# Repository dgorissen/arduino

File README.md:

# arduino
Misc arduino projects

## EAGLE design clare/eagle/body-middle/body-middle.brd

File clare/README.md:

# C.L.A.R.E - Come Look At Robot Entertainment

CLARE, short for Come Look At Robot Entertainment, is an interactive robot I designed together with the kids and have been working on (and still am) for quite some time. Its mostly for fun and to expose the kids to robotics but also allows me to scratch that technical itch as my professional life ventures into documents, spreadsheets, powerpoint, and meetings.

I am designing CLARE fully from scratch, including all CAD, wiring, coding, custom PCBs, etc. Printing happens on my home 3D printer and features multiple cameras, face recognition and tracking, interactive voice commands, LCD screen, LEDs, and fart detector. It can be controlled with an RC remote or (planned) move autonomously using SLAM.

This is still a work in progress and updates will come whenever I find a pocket of time.

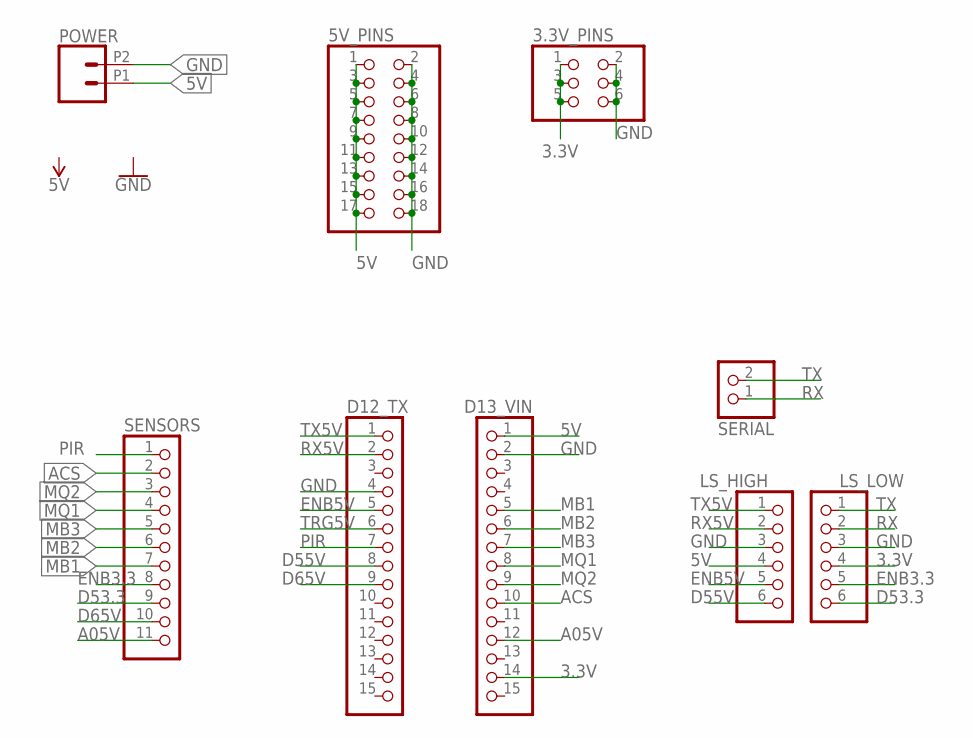
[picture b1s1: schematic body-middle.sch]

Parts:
3.3V_PINS: PINHD-2X3; 2X03
5V_PINS: PINHD-2X9; 2X09
D12_TX, D13_VIN: PINHD-1X15; 1X15
LS_HIGH: PINHD-1X6; 1X06
LS_LOW: PINHD-1X6; 1X06
POWER: CONN_022.54MM_SCREWTERM; 1X02_2.54_SCREWTERM
SENSORS: PINHD-1X11; 1X11
SERIAL: PINHD-1X2; 1X02

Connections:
3.3V: 3.3V_PINS.1, 3.3V_PINS.3, 3.3V_PINS.5, D13_VIN.14, LS_LOW.4
5V: 5V_PINS.1, 5V_PINS.3, 5V_PINS.5, 5V_PINS.7, 5V_PINS.9, 5V_PINS.11, 5V_PINS.13, 5V_PINS.15, 5V_PINS.17, D13_VIN.1, LS_HIGH.4, POWER.P1 (1)
A05V: D13_VIN.12, SENSORS.11
ACS: D13_VIN.10, SENSORS.2
D53.3: LS_LOW.6, SENSORS.9
D55V: D12_TX.8, LS_HIGH.6
D65V: D12_TX.9, SENSORS.10
ENB3.3: LS_LOW.5, SENSORS.8
ENB5V: D12_TX.5, LS_HIGH.5
GND: 3.3V_PINS.2, 3.3V_PINS.4, 3.3V_PINS.6, 5V_PINS.2, 5V_PINS.4, 5V_PINS.6, 5V_PINS.8, 5V_PINS.10, 5V_PINS.12, 5V_PINS.14, 5V_PINS.16, 5V_PINS.18, D12_TX.4, D13_VIN.2, LS_HIGH.3, LS_LOW.3, POWER.P2 (2)
MB1: D13_VIN.5, SENSORS.7
MB2: D13_VIN.6, SENSORS.6
MB3: D13_VIN.7, SENSORS.5
MQ1: D13_VIN.8, SENSORS.4
MQ2: D13_VIN.9, SENSORS.3
PIR: D12_TX.7, SENSORS.1
RX: LS_LOW.2, SERIAL.1
RX5V: D12_TX.2, LS_HIGH.2
TRG5V: D12_TX.6
TX: LS_LOW.1, SERIAL.2
TX5V: D12_TX.1, LS_HIGH.1

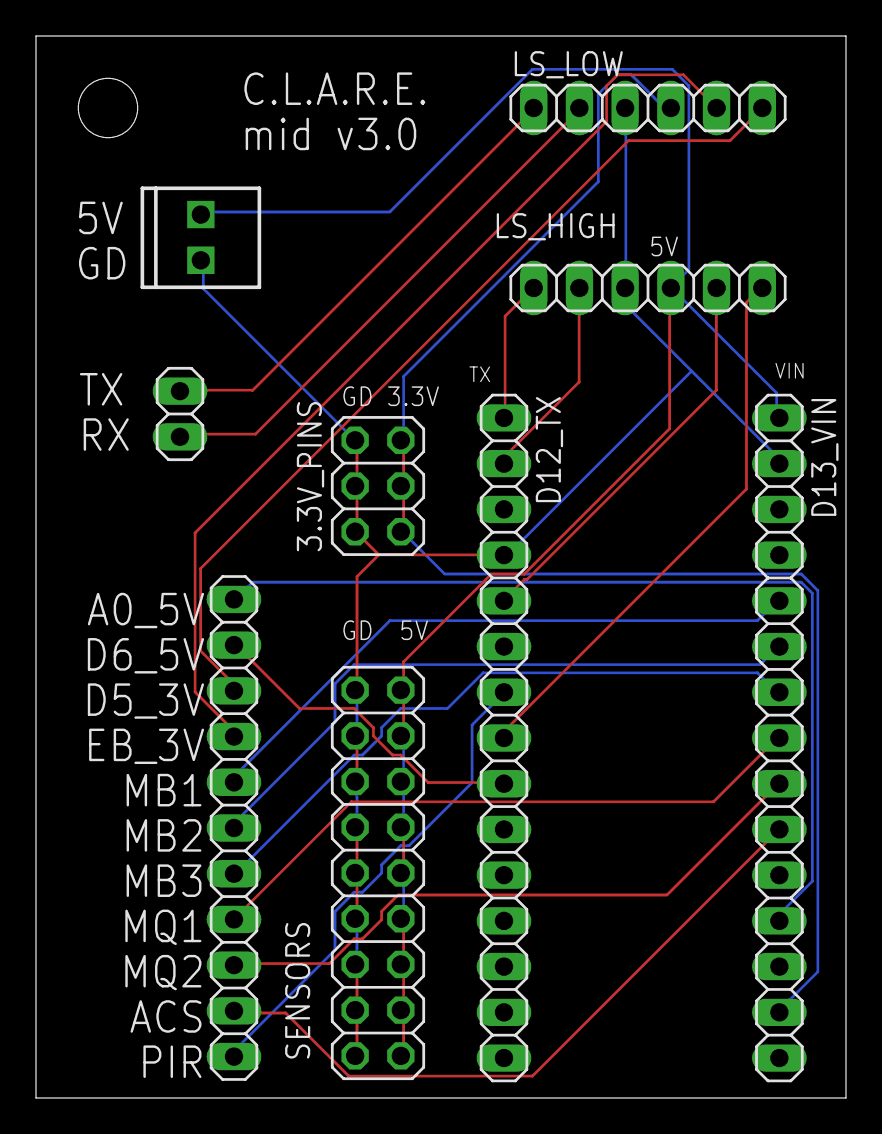
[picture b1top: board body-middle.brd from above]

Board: 2 copper layers, 45.0 x 59.0 mm, 9 parts (0 on the bottom side), 20 nets.

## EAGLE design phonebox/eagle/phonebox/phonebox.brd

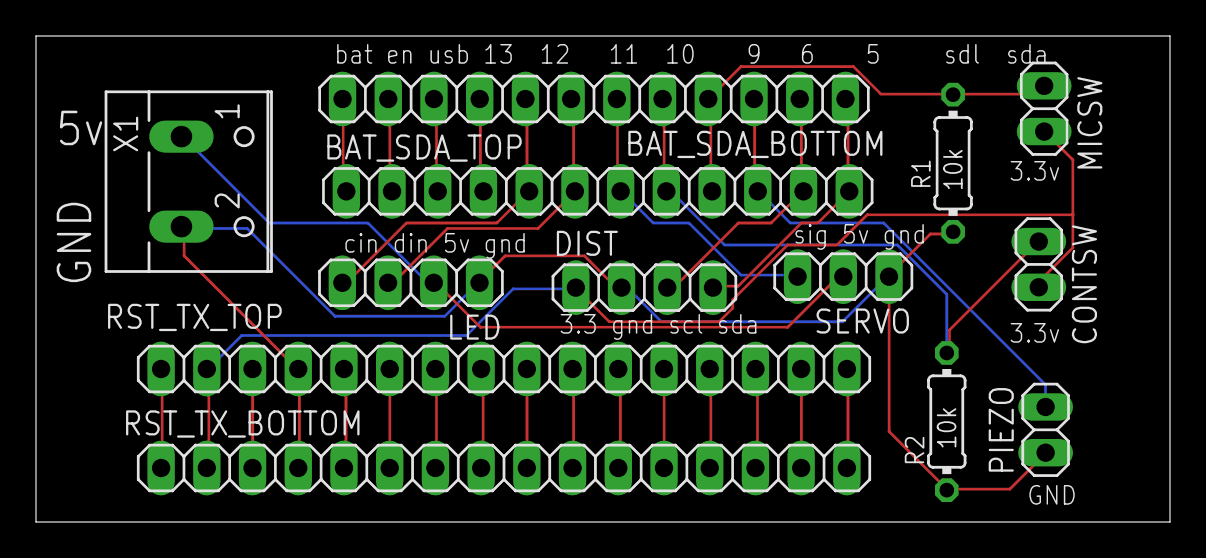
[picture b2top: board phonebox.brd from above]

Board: 2 copper layers, 63.0 x 27.0 mm, 13 parts (0 on the bottom side), 29 nets.

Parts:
BAT_SDA_BOTTOM: 1X12
BAT_SDA_TOP: 1X12
CONTSW: 1X02
DIST: 1X04
LED: 1X04
MICSW: 1X02
PIEZO: 1X02
R1, R2: 10k; 0204/7
RST_TX_BOTTOM: 1X16
RST_TX_TOP: 1X16
SERVO: 1X03
X1: W237-102

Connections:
3.3V: CONTSW.1, DIST.1, MICSW.1, RST_TX_BOTTOM.2, RST_TX_TOP.2
5V: LED.2, SERVO.2, X1.1
CONTSW: BAT_SDA_BOTTOM.5, BAT_SDA_TOP.8, CONTSW.2, R2.2
GND: DIST.2, LED.1, PIEZO.1, R1.1, R2.1, RST_TX_BOTTOM.4, RST_TX_TOP.4, SERVO.1, X1.2
LED_CIN: BAT_SDA_BOTTOM.8, BAT_SDA_TOP.5, LED.4
LED_DIN: BAT_SDA_BOTTOM.7, BAT_SDA_TOP.6, LED.3
MICSW: BAT_SDA_BOTTOM.4, BAT_SDA_TOP.9, MICSW.2, R1.2
unnamed: RST_TX_BOTTOM.1, RST_TX_TOP.1
unnamed: RST_TX_BOTTOM.3, RST_TX_TOP.3
unnamed: RST_TX_BOTTOM.5, RST_TX_TOP.5
unnamed: RST_TX_BOTTOM.6, RST_TX_TOP.6
unnamed: RST_TX_BOTTOM.7, RST_TX_TOP.7
unnamed: RST_TX_BOTTOM.8, RST_TX_TOP.8
unnamed: RST_TX_BOTTOM.9, RST_TX_TOP.9
unnamed: RST_TX_BOTTOM.10, RST_TX_TOP.10
unnamed: RST_TX_BOTTOM.11, RST_TX_TOP.11
unnamed: RST_TX_BOTTOM.12, RST_TX_TOP.12
unnamed: RST_TX_BOTTOM.13, RST_TX_TOP.13
unnamed: RST_TX_BOTTOM.14, RST_TX_TOP.14
unnamed: RST_TX_BOTTOM.15, RST_TX_TOP.15
unnamed: RST_TX_BOTTOM.16, RST_TX_TOP.16
unnamed: BAT_SDA_BOTTOM.12, BAT_SDA_TOP.1
unnamed: BAT_SDA_BOTTOM.11, BAT_SDA_TOP.2
unnamed: BAT_SDA_BOTTOM.10, BAT_SDA_TOP.3
unnamed: BAT_SDA_BOTTOM.9, BAT_SDA_TOP.4
PIEZZO: BAT_SDA_BOTTOM.3, BAT_SDA_TOP.10, PIEZO.2
SCL: BAT_SDA_BOTTOM.2, BAT_SDA_TOP.11, DIST.3
SDA: BAT_SDA_BOTTOM.1, BAT_SDA_TOP.12, DIST.4
SERVO: BAT_SDA_BOTTOM.6, BAT_SDA_TOP.7, SERVO.3

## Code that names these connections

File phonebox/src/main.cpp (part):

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const int ALARM_DURATION = 1000*60*3;
constexpr float PHONE_DIST = 48.5f;

const int SERVO_PIN = 10;
const int LED_DIN_PIN = 11;
const int LED_CIN_PIN = 12;
const int PIEZZO_PIN = 5;
const int MIC_SWITCH_PIN = 6;
const int CONT_SWITCH_PIN = 9;

VL53L1X dist_sensor;
bool dist_sensor_ok = false;
//Adafruit_NeoPixel status_led = Adafruit_NeoPixel(1, PIN_NEOPIXEL, NEO_GRB);
Adafruit_DotStar strip = Adafruit_DotStar(20, LED_DIN_PIN, LED_CIN_PIN, DOTSTAR_BGR);

const uint32_t orange = strip.Color(255, 165, 0);
const uint32_t red = strip.Color(255, 0, 0);
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
void setup_servo(){
  ESP32_ISR_Servos.useTimer(3);
  servoIndex1 = ESP32_ISR_Servos.setupServo(SERVO_PIN, 500, 2500);
  
  if (servoIndex1 != -1){
    Serial.println(F("Servo setup OK"));
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  setup_dist_sensor();
  setup_servo();

  pinMode(PIEZZO_PIN, OUTPUT);
  pinMode(MIC_SWITCH_PIN, INPUT);
  pinMode(CONT_SWITCH_PIN, INPUT);

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    // to calculate the note duration, take one second divided by the note type.
    //e.g. quarter note = 1000 / 4, eighth note = 1000/8, etc.
    int noteDuration = 1000 / durations[thisNote];
    tone(PIEZZO_PIN, melody[thisNote], noteDuration);

    // to distinguish the notes, set a minimum time between them.
    // the note's duration + 30% seems to work well:
    int pauseBetweenNotes = noteDuration * 1.30;
    delay(pauseBetweenNotes);
    // stop the tone playing:
    noTone(PIEZZO_PIN);
  }
}

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
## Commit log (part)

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2020-03-06 Add hungrybot code
2020-03-15 Basic facial expressions working
2021-01-07 Useless box, initial commit, working build
2021-01-07 Move library files to lib folders
2021-01-11 Add util function
2021-01-11 Got it to work on robot, not 100% about calclation method but seems ok
2021-01-11 Update comments
2021-01-11 Add comments
2021-01-14 Handle reversing a bit more intuitively
2021-02-20 As run on the first RC session
2021-03-05 - Add basic publishing over Serial5 for future comms testing - Properly read and publish motor encoders - Turn headlights on except when going backwards Tested on robot
2021-03-14 Update bootstrap
2021-03-14 Update docker commands to fit hub repo
2021-03-16 Working docker up to cv2.__version__
2021-03-21 Install x2go, setup ssh, start flask hello world
2021-03-21 Install node
2021-03-21 Scaffolding connecting flask and vue app based of template. Seems to work
2021-04-04 Fix typo
2021-04-04 Fix syntax error
2021-04-04 Various fixes as part of testing on pi, not quite there yet
2021-04-04 Fix arch detection
2021-04-04 Better arch detect
2021-04-04 Add clean target
2021-04-04 Fix param passing to rosserial
2021-04-04 Add missing self params
2021-04-04 Use ~ instead of abs path
2021-04-04 Give roscore some time to start
2021-04-13 As successsfully built and run (cbrain container)
2021-04-13 Add workspace
2021-04-13 Dont ignore lib
2021-04-13 First pass of formally pubhlishing a state object over ros. Not tested on robot yet.
2021-04-14 Add missing newlines to log messages
2021-04-14 Fix wrong channel assignment, changed state serialisation to String Successful end-2-end headlights control from REST call, through ROS
2021-04-15 Structured way of receicing commands through a state_in object Some code cleanup All seems to work, failsafe handling still needs fixing
2021-04-15 Cleaner mode setting in output state
2021-04-15 No need for safestring
2021-04-15 Change headlight message to match teensy changes
2021-04-15 Add not connected check
2021-04-16 Cleanup of webapp, now single card for Tracks with some basic functions Tested locally, not yet on robot
2021-04-16 End-2-end card-robot tested and works!
2021-04-16 Set page title
2021-04-17 Compile openvino smaples and download model
2021-04-18 ros export vars are needed for master, not rosserial
2021-04-18 Reduce roscore waittime to 3s
2021-04-18 Add gpio device
2021-05-03 Add support for realsense, adafruit sound bonnet, respeaker, piwatcher Docker builds, just needs cleanup
2021-06-23 Fix comments in bashrc, add some pkgs
2021-06-23 Add x11-apps
2021-06-23 Add ultrasound reading code for xiao
2021-07-13 Add NCS test
2021-07-13 Bump versions, update / fix pyenv working on librealsense
2021-07-13 Set correct usb for tracks
2021-07-21 Added body middle eagle files as submitted to allpcb
2021-07-21 Working realsense
2021-08-07 New arduino nano pcb for body middle with working code
2021-08-07 Add comment to install missing package
2021-08-07 Add ros node for clare middle serial stream
2021-08-07 Add timeout to clare_body_middle.py and dont immediately fail on float conversion
2021-08-07 No need for track port variables as /dev is mounted
2021-08-07 Add middle node launch command
2021-08-07 Log before starting each command, put sleeps in between, and tail rosout
2021-08-08 Cleaned up tracks a bit, added middle, not tested yet
2021-08-08 Put connected guard on /connect
2021-08-08 Set connected status correctly on page load
2021-08-08 Add working card for middle
2021-08-09 Increase time waiting for roscore to start
2021-08-20 Set default python interpreter in workspace
2021-08-20 Use EventSources for track/middle state, not tested yet
2021-08-28 Increase time to wait for ros master to start to 5s
2021-08-28 Fix event streaming, verified working with Tracks and Middle on robot
2021-08-28 Use Server Side Events for communicating states (#1)
    * Set default python interpreter in workspace
    * Use EventSources for track/middle state, not tested yet
    * Remove contradictory comment
    * Increase time to wait for ros master to start to 5s
    * Fix event streaming, verified working with Tracks and Middle on robot
2021-08-28 Start thinking about face detection on camera stream, initial untested snippets
2021-08-29 Update dockerfile, work around cmake install issue & add pkgs
2021-08-29 Cant pip install opengl
2021-09-04 Make x fwding work from inside docker container
2021-09-04 face_detect.py now works in docker as standalone script
2021-09-04 Make openvino movidius test command work on copy paste
2021-09-04 Remove non existant mssage file
2021-09-04 Move eyes out of head to top level clare folder
2021-09-04 Fix grammar
2021-09-04 Add name attribute (auto generated)
2021-09-05 Make face detection work with AsyncPipeline, with 2 output topics, tested
2021-09-05 Update Dockerfile, plain output when building
2021-09-05 Video feed now shows nicely in browser but some sudden issue with cv2 not being found on backend startup in entrypoint
2021-09-06 Start head camera feed in entrypoint, resolved cv2 issue in entrypoint
2021-09-07 Reordered for faster builds, removed xfce, added sound related python pkgs
2021-09-12 Add respeaker rules info
2021-09-12 Add TTS tools
2021-09-12 Add speech recognition nodes to the entry point
2021-09-15 Add respeaker & TTS pkgs and nodes
2021-09-15 First wiring up of TTS and STT with web ui, not tested
2021-09-18 Speak to me button works
2021-09-18 Add flag to start just container & rosmaster
2021-09-18 Remove simplemode
2021-09-19 STT nodes should now work
2021-09-19 Fix wrong stream name in client and just return top transcript in app
2021-09-19 Fix transcript rendering in text area and always scroll to bototm
2021-09-19 Store cmd in variable
2021-09-19 Add bonnet setup script
2021-09-19 Update/re-org Dockerfile
2021-09-25 Refactor state wrappers into single file and add one for realsense depth
2021-09-25 Add missing state.py
2021-09-25 Working depth feed
2021-09-25 Add depth view to web page, works
2021-09-26 Teensy tracks code changes to receive driving commands over ROS, not tested yet
2021-10-18 Remove alsa card preference from bashrc after removal of sound bonnet
2021-10-18 Ensure we always publish commands as ints
2021-11-07 Set output card in tts
2021-11-07 Start ros node in own thread
2021-12-08 Add /boot/config.txt
2021-12-11 Bump axios from 0.21.1 to 0.21.2 in /clare/brain/client
    Bumps [axios](https://github.com/axios/axios) from 0.21.1 to 0.21.2.
    - [Release notes](https://github.com/axios/axios/releases)
    - [Changelog](https://github.com/axios/axios/blob/master/CHANGELOG.md)
    - [Commits](https://github.com/axios/axios/compare/v0.21.1...v0.21.2)
    ---
    updated-dependencies:
2021-12-11 Add adafruit libs
2021-12-13 Mount /run/udev/data so libinput should work
2021-12-14 Update docker & bootstrap files as part of getting top working
2021-12-14 More tweaks to get top working
2021-12-15 Mount /sys/class/gpio just in case
2021-12-15 Expose environmentals
2021-12-17 Add simple buttons node for testing
2021-12-18 Button node woks now
2021-12-18 Node doesnt ignore signals and set node name
2021-12-18 Working ir node
2021-12-19 Add working launch file
2021-12-19 Update boot config to what is running
2021-12-19 Bring head camera node in line with other nodes
2021-12-19 split ros_pkgs into ros_build and ros_install targets
2021-12-19 Launch file now covers all nodes
2021-12-19 Ensure jsk_3rdparty respeaker_ros is installed
2021-12-19 Temporarily disable top state and update images topic name
2021-12-19 Fix wrong channel name
2021-12-19 Ensure ctrl-c shuts down node
2021-12-20 All nodes now start properly in entrypoint Only backend crashes due to missing cv2..
2021-12-20 openvino environment needs to be sourced before running backend (for python libs)
2021-12-30 First versions of remaining body top nodes, not tested yet
2022-01-03 Fix catkin build and running of new nodes
2022-01-03 Enable passwordless sudo
2022-01-03 Mute/unmute amp when talking. Remove obsolete ClareTop state stuff
2022-01-03 Moved ros pub/sub inside states. Unmute by default
2022-01-03 Add makefile commands to build/upload tracks/teensy
2022-01-03 We need teensy cli & udev rules
2022-01-03 Setup environment once for all tasks in entrypoint
2022-01-03 Ignore unused vars
2022-01-03 Add placeholder top.png file
2022-01-03 Support returning top state
2022-01-04 Set top image
2022-01-04 Set initial lightring value
2022-01-04 Cleanup card layout and remove photo stuff
2022-01-04 remove photo stuff
2022-01-04 Cleanup gpio on exit
2022-01-04 Nicer handling of off state
2022-01-04 Rosify ultrasound project and refactor into clare_middle. Not tested yet.
2022-01-04 Add msg files
2022-01-04 Fix compilation errors
2022-01-05 Ros and arduino nano dont play well together, reverted back to serial
2022-01-05 Synced up middle_node with arduino code, not tested yet
2022-01-05 Middle node fully working again
2022-01-05 Remove ultrasound dir
2022-01-05 Remove unused printvals
2022-01-05 Update backend to new middle node
2022-01-05 Fix catkin build
2022-01-05 Fix compilation
2022-01-05 TX SE switch allows for manually overriding any sw commands
2022-01-05 Publish motor direction and only publish if changed
2022-01-05 Swap left/right encoder to match hardware, remove unused publish fcns
2022-01-05 Update webapp to new tracks topics
2022-01-05 Reduce queue size
2022-01-05 Use .data on ros msgs
2022-01-05 Fix serialisation errors
2022-01-06 Fix logging call
2022-01-06 Make it possible to run in minimal (rosmaster only mode)
2022-01-07 Use SPI for light ring to avoid clash with audio
2022-01-07 Lightring moved to spi, USB devices have changed, get everything running again
2022-01-07 Setup spi usage
2022-01-10 USB devices changed. All components verified working
2022-01-11 Refactored directory structure, not tested yet
2022-01-11 Bump axios from 0.21.1 to 0.21.2 in /clare/interface/client
    Bumps [axios](https://github.com/axios/axios) from 0.21.1 to 0.21.2.
    - [Release notes](https://github.com/axios/axios/releases)
    - [Changelog](https://github.com/axios/axios/blob/master/CHANGELOG.md)
    - [Commits](https://github.com/axios/axios/compare/v0.21.1...v0.21.2)
    ---
    updated-dependencies:
2022-01-11 Clare has now moved into its own repo
2022-02-09 Add magic 8 ball code
2022-02-11 Use program memory to store more strings
2022-06-15 Add fishfeeder, rover, tvbgone
2022-07-17 Platformio-ify hungrybot and slight cleanup
2022-07-30 Tweak down pos for new build
2023-02-18 Add test loop, remove unused flags
2023-03-05 All functions seem to work
2023-03-05 Add calendar app script
2023-05-04 Fix lock time calculation
2023-08-05 Format
2023-08-05 Case insensitive calendar entry comparison
2024-06-30 Bump requests from 2.21.0 to 2.32.2 in /worldview
    Bumps [requests](https://github.com/psf/requests) from 2.21.0 to 2.32.2.
    - [Release notes](https://github.com/psf/requests/releases)
    - [Changelog](https://github.com/psf/requests/blob/main/HISTORY.md)
    - [Commits](https://github.com/psf/requests/compare/v2.21.0...v2.32.2)
    ---
    updated-dependencies:
2024-06-30 Fix paths
2024-07-20 Move images into own folder
2024-07-20 Fullscreen
2024-07-20 add gifs
2024-07-20 reduce gif sizes
2024-07-20 Allow access to web page from remote hosts, add/shrink gifs
2024-07-20 remove dragon gif
2024-07-28 show datetime on epic image
2024-08-03 Add support for RAMMB
2024-08-04 Set displayed timezone to UK
2024-09-01 Avoid lock alarming on the last day
2024-09-01 Keep locked for an extra hour on weekends
2024-09-01 Extend alarm duration
2024-09-01 Ignore dist sensor given the different phones
2024-09-08 Add params to set zoom level & tile filters on rammb urls
2024-09-08 Add print statements
2024-09-08 Add a zoom in of Europe as part of the carousel
2024-09-09 Fix syntax errors
2024-10-12 Delay weekend unlock by 30min
2024-12-15 Properly handle daylight savings time
2025-08-02 Change unlock times
2025-08-02 Cleanup calender script
2025-08-02 Store locked state in preference
2025-10-25 Fix time based logic not being followed
2025-10-25 Add tamper alarm
2026-02-27 Robustify worldview
2026-05-11 Cleanup

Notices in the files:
parts and their libraries:
SparkFun-Connectors: Licensing: Creative Commons ShareAlike 4.0 International - https://creativecommons.org/licenses/by-sa/4.0
